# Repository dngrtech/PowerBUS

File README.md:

# PowerBUS
Eurorack power distribution busboard with 14 connectors has all 3 power rails (-12, +12, +5) and indicator LED per rail. It is supposed to be used with shrouded keyed 16-pin connectors. The power inlets has an option - either standard 6.3mm Faston connector or standard wire terminal block with 2.54 mm contact spacing. 
Consider spending extra for 2+ oz copper traces for improved performance.

# License
Hardware design licensed under cc-by-sa-3.0

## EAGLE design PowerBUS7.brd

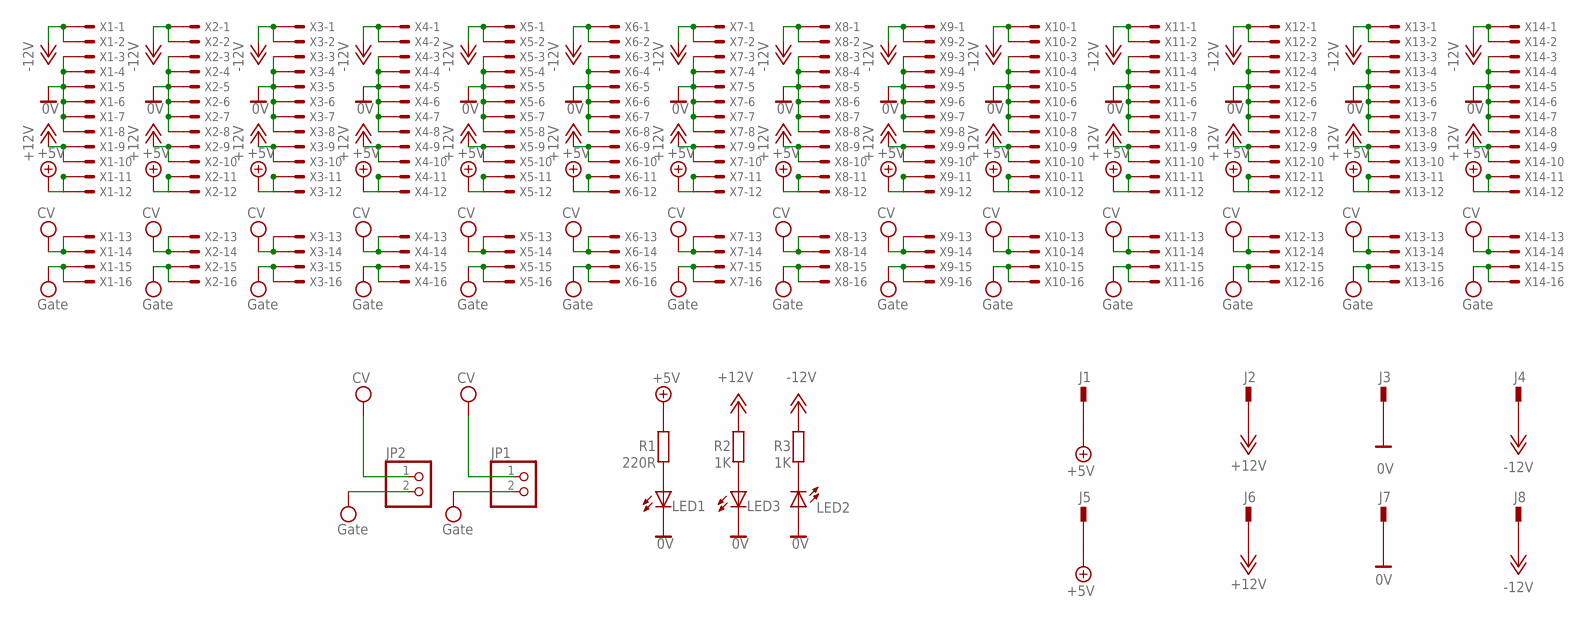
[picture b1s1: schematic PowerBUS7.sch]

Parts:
J1, J2, J3, J4, J5, J6, J7, J8: PIN2F061.040; F061.040
JP1, JP2: PINHD-1X2; 1X02
LED1, LED2, LED3: LED5MM
R1: 220R; 0204/5
R2, R3: 1K; 0204/5
X1, X2, X3, X4, X5, X6, X7, X8, X9, X10, X11, X12, X13, X14: 057-016-1

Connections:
0V: J3.A1, J3.A2, J7.A1, J7.A2, LED1.K (C), LED2.A, LED3.K (C), X1.3, X1.4, X1.5, X1.6, X1.7, X1.8, X2.3, X2.4, X2.5, X2.6, X2.7, X2.8, X3.3, X3.4, X3.5, X3.6, X3.7, X3.8, X4.3, X4.4, X4.5, X4.6, X4.7, X4.8, X5.3, X5.4, X5.5, X5.6, X5.7, X5.8, X6.3, X6.4, X6.5, X6.6, X6.7, X6.8, X7.3, X7.4, X7.5, X7.6, X7.7, X7.8, X8.3, X8.4, X8.5, X8.6, X8.7, X8.8, X9.3, X9.4, X9.5, X9.6, X9.7, X9.8, X10.3, X10.4, X10.5, X10.6, X10.7, X10.8, X11.3, X11.4, X11.5, X11.6, X11.7, X11.8, X12.3, X12.4, X12.5, X12.6, X12.7, X12.8, X13.3, X13.4, X13.5, X13.6, X13.7, X13.8, X14.3, X14.4, X14.5, X14.6, X14.7, X14.8
+5V: J1.A1, J1.A2, J5.A1, J5.A2, R1.2, X1.11, X1.12, X2.11, X2.12, X3.11, X3.12, X4.11, X4.12, X5.11, X5.12, X6.11, X6.12, X7.11, X7.12, X8.11, X8.12, X9.11, X9.12, X10.11, X10.12, X11.11, X11.12, X12.11, X12.12, X13.11, X13.12, X14.11, X14.12
+12V: J2.A1, J2.A2, J6.A1, J6.A2, R2.2, X1.9, X1.10, X2.9, X2.10, X3.9, X3.10, X4.9, X4.10, X5.9, X5.10, X6.9, X6.10, X7.9, X7.10, X8.9, X8.10, X9.9, X9.10, X10.9, X10.10, X11.9, X11.10, X12.9, X12.10, X13.9, X13.10, X14.9, X14.10
-12V: J4.A1, J4.A2, J8.A1, J8.A2, R3.2, X1.1, X1.2, X2.1, X2.2, X3.1, X3.2, X4.1, X4.2, X5.1, X5.2, X6.1, X6.2, X7.1, X7.2, X8.1, X8.2, X9.1, X9.2, X10.1, X10.2, X11.1, X11.2, X12.1, X12.2, X13.1, X13.2, X14.1, X14.2
unnamed: LED2.K (C), R3.1
unnamed: LED1.A, R1.1
unnamed: LED3.A, R2.1
VPP: JP1.1, JP2.1, X1.13, X1.14, X2.13, X2.14, X3.13, X3.14, X4.13, X4.14, X5.13, X5.14, X6.13, X6.14, X7.13, X7.14, X8.13, X8.14, X9.13, X9.14, X10.13, X10.14, X11.13, X11.14, X12.13, X12.14, X13.13, X13.14, X14.13, X14.14
VSS: JP1.2, JP2.2, X1.15, X1.16, X2.15, X2.16, X3.15, X3.16, X4.15, X4.16, X5.15, X5.16, X6.15, X6.16, X7.15, X7.16, X8.15, X8.16, X9.15, X9.16, X10.15, X10.16, X11.15, X11.16, X12.15, X12.16, X13.15, X13.16, X14.15, X14.16

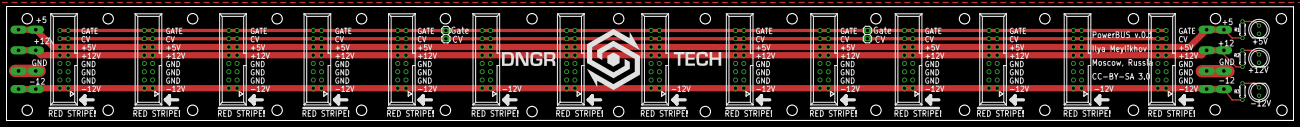
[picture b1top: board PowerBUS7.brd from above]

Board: 2 copper layers, 396.2 x 35.1 mm, 30 parts (0 on the bottom side), 9 nets.

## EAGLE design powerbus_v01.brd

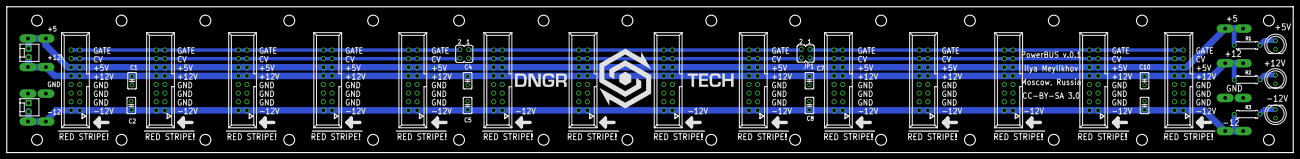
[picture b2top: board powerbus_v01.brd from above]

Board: 2 copper layers, 379.4 x 43.0 mm, 40 parts (0 on the bottom side), 9 nets.

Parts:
C1: 1u; C025-025X050
C2, C4, C5, C7, C8, C10, C11: 1u tantalio; C025-025X050
J1, J2, J3, J4, J5, J6, J7, J8: PIN2F061.040; F061.040
J9, J10: MOLEX-1X2
JP1, JP5: JP2Q
LED1, LED2, LED3: LED5MM
R1: 220R; 0207/7
R2, R3: 1K; 0207/7
X1, X2, X3, X4, X5, X6, X7, X8, X9, X10, X11, X12, X13, X14: 057-016-1

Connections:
0V: C1.2, C2.1, C4.2, C5.1, C7.2, C8.1, C10.2, C11.1, J3.A1, J3.A2, J7.A1, J7.A2, J10.1, LED1.K, LED2.A, LED3.K, X1.3, X1.4, X1.5, X1.6, X1.7, X1.8, X2.3, X2.4, X2.5, X2.6, X2.7, X2.8, X3.3, X3.4, X3.5, X3.6, X3.7, X3.8, X4.3, X4.4, X4.5, X4.6, X4.7, X4.8, X5.3, X5.4, X5.5, X5.6, X5.7, X5.8, X6.3, X6.4, X6.5, X6.6, X6.7, X6.8, X7.3, X7.4, X7.5, X7.6, X7.7, X7.8, X8.3, X8.4, X8.5, X8.6, X8.7, X8.8, X9.3, X9.4, X9.5, X9.6, X9.7, X9.8, X10.3, X10.4, X10.5, X10.6, X10.7, X10.8, X11.3, X11.4, X11.5, X11.6, X11.7, X11.8, X12.3, X12.4, X12.5, X12.6, X12.7, X12.8, X13.3, X13.4, X13.5, X13.6, X13.7, X13.8, X14.3, X14.4, X14.5, X14.6, X14.7, X14.8
+5V: J1.A1, J1.A2, J5.A1, J5.A2, J9.1, R1.2, X1.11, X1.12, X2.11, X2.12, X3.11, X3.12, X4.11, X4.12, X5.11, X5.12, X6.11, X6.12, X7.11, X7.12, X8.11, X8.12, X9.11, X9.12, X10.11, X10.12, X11.11, X11.12, X12.11, X12.12, X13.11, X13.12, X14.11, X14.12
+12V: C1.1, C4.1, C7.1, C10.1, J2.A1, J2.A2, J6.A1, J6.A2, J9.2, R2.2, X1.9, X1.10, X2.9, X2.10, X3.9, X3.10, X4.9, X4.10, X5.9, X5.10, X6.9, X6.10, X7.9, X7.10, X8.9, X8.10, X9.9, X9.10, X10.9, X10.10, X11.9, X11.10, X12.9, X12.10, X13.9, X13.10, X14.9, X14.10
-12V: C2.2, C5.2, C8.2, C11.2, J4.A1, J4.A2, J8.A1, J8.A2, J10.2, R3.2, X1.1, X1.2, X2.1, X2.2, X3.1, X3.2, X4.1, X4.2, X5.1, X5.2, X6.1, X6.2, X7.1, X7.2, X8.1, X8.2, X9.1, X9.2, X10.1, X10.2, X11.1, X11.2, X12.1, X12.2, X13.1, X13.2, X14.1, X14.2
unnamed: LED2.K, R3.1
unnamed: LED1.A, R1.1
unnamed: LED3.A, R2.1
VPP: JP1.3, JP1.4, JP5.3, JP5.4, X1.13, X1.14, X2.13, X2.14, X3.13, X3.14, X4.13, X4.14, X5.13, X5.14, X6.13, X6.14, X7.13, X7.14, X8.13, X8.14, X9.13, X9.14, X10.13, X10.14, X11.13, X11.14, X12.13, X12.14, X13.13, X13.14, X14.13, X14.14
VSS: JP1.1, JP1.2, JP5.1, JP5.2, X1.15, X1.16, X2.15, X2.16, X3.15, X3.16, X4.15, X4.16, X5.15, X5.16, X6.15, X6.16, X7.15, X7.16, X8.15, X8.16, X9.15, X9.16, X10.15, X10.16, X11.15, X11.16, X12.15, X12.16, X13.15, X13.16, X14.15, X14.16

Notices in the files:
parts and their libraries:
SparkFun-Connectors: Licensing: Creative Commons ShareAlike 4.0 International - https://creativecommons.org/licenses/by-sa/4.0
